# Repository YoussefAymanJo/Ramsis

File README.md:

# Ramsis
## Description
Desk Robot, your daily companion, can answer any question you ask about weather, news, or even songs. it powered by ESP32 S3. and has lovely face interact with you
## Why it was built
Actually,i feel boring and uncomfortable on my studying and working hours on my study or on pc.so,i made this robot to be ai companion for me. Interact with my emotiions and answer my questions.this robot mainly for entertainment and rapid helper companion in any quetion look like Jarvis.
## How to use it / Build it
first, fabricate and print pcb,then print 3d models,and wire circuit and test it.then assemlbe all together and test again.
## Schematic
I made a schematic for my keyboard, and sketch simpled diagram for schematic.

## PCB
I outlined shape first,the routed the pcb and added 3d models

Wiring Diagram :

## CAD
I started  sketching the enclosure based on the PCB, then made the top cover, added openings, and assembled.

## Firmware
i will us this for firmware https://github.com/78/xiaozhi-esp32 and https://github.com/EDISON-SCIENCE-CORNER/AI-CHAT-BOT/tree/main/3D%20FILES  while editing the code while building.
## BOM 
I made the BOM  and needed materials ,in egypt then convert its price to USD dollar.

## Zine

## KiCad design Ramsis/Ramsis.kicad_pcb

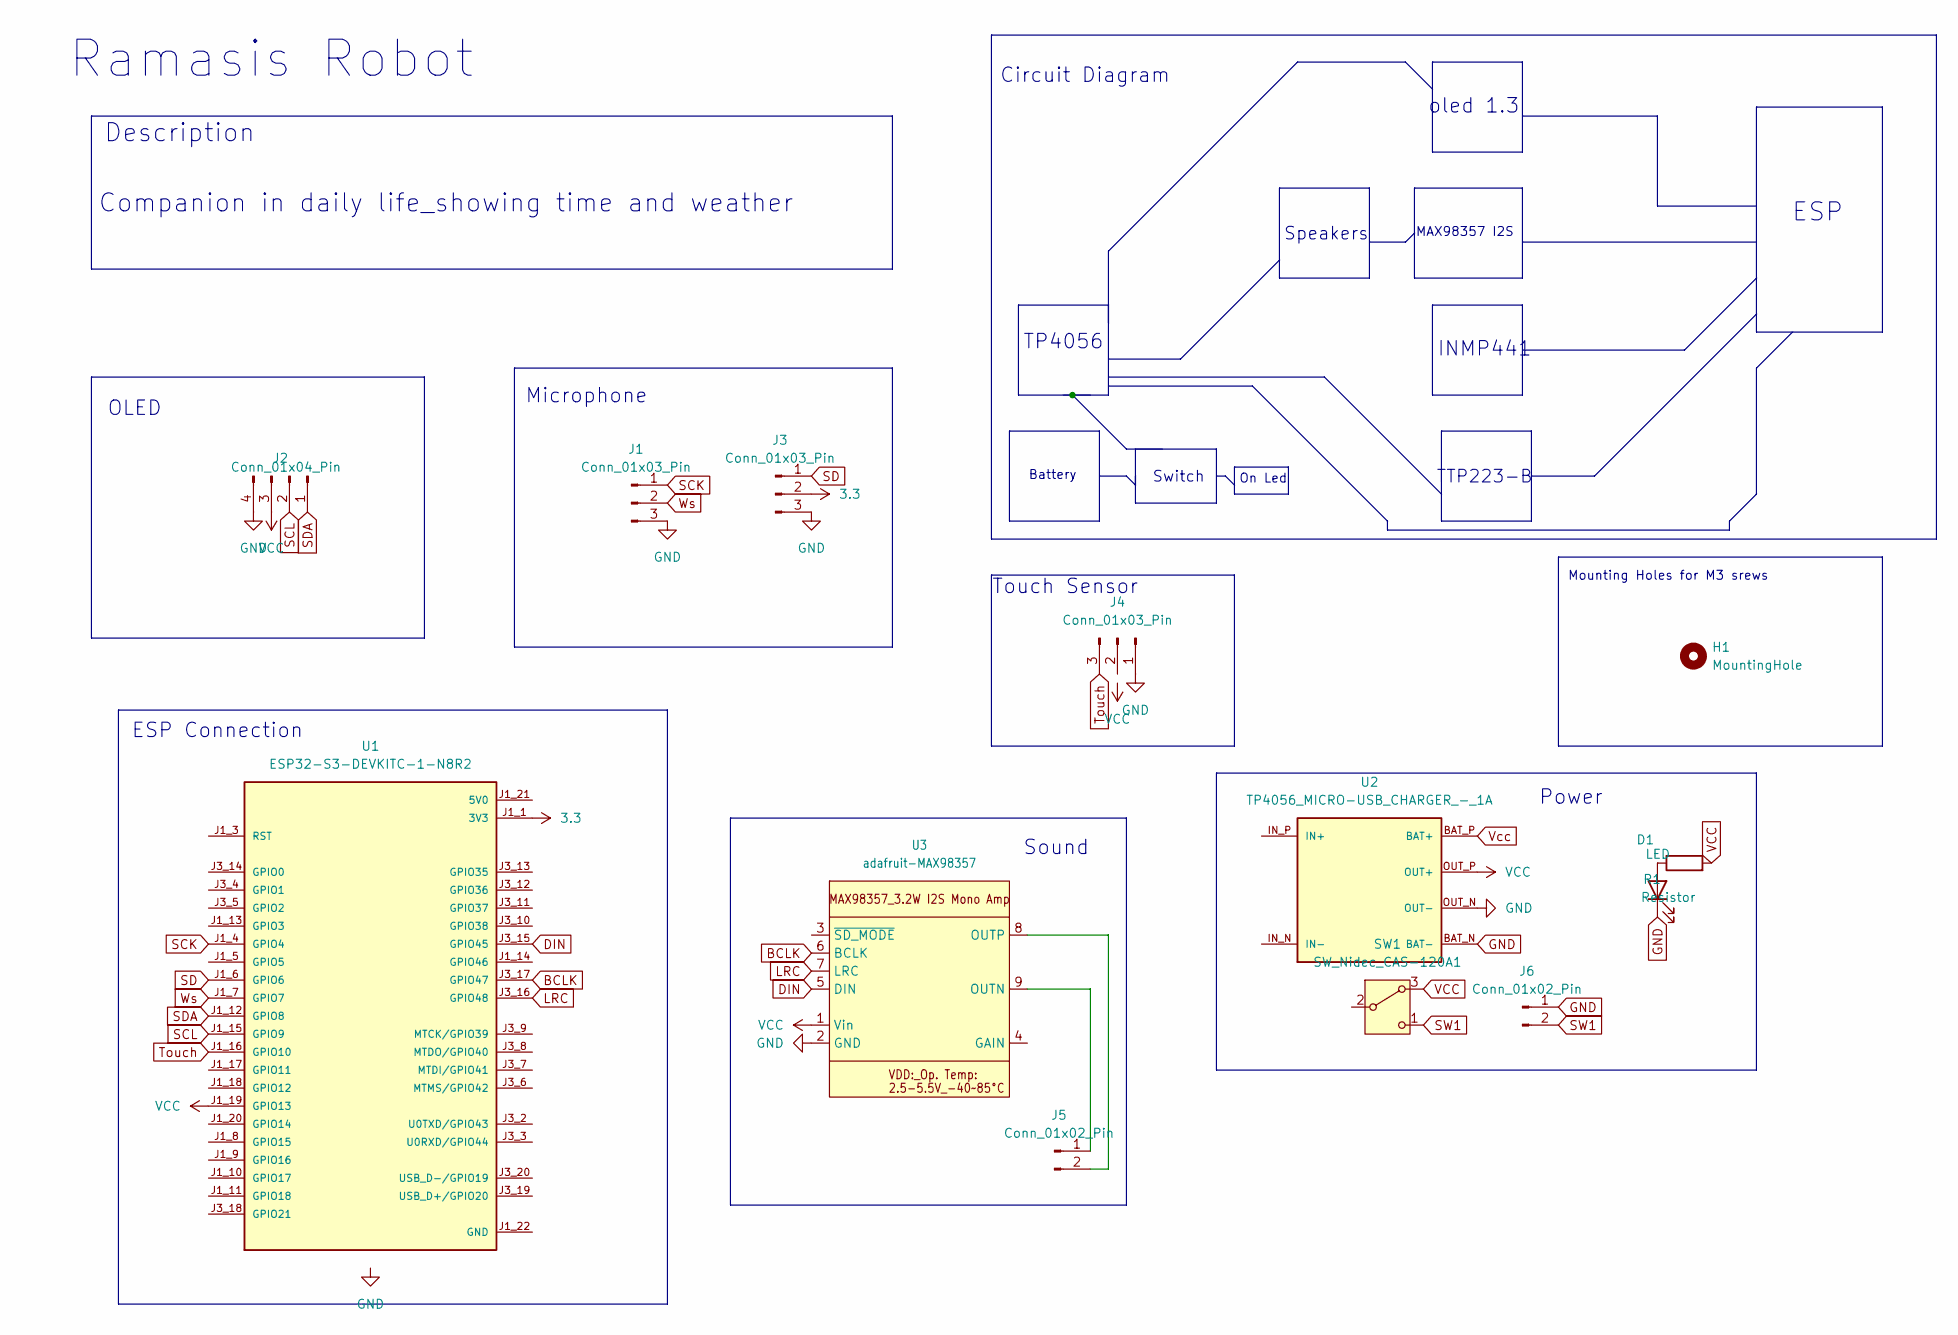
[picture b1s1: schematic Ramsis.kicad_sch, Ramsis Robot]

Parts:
D1: LED; LED_D3.0mm
H1: MountingHole; MountingHole_3.2mm_M3
J1, J3, J4: Conn_01x03_Pin; PinHeader_1x03_P2.00mm_Vertical
J2: Conn_01x04_Pin; PinHeader_1x04_P2.00mm_Vertical
J5, J6: Conn_01x02_Pin; JST_PH_S2B-PH-K_1x02_P2.00mm_Horizontal
R1: Resistor; R_Axial_DIN0204_L3.6mm_D1.6mm_P5.08mm_Horizontal
SW1: SW_Nidec_CAS-120A1; SW_Slide_SPDT_Angled_CK_OS102011MA1Q
U1: ESP32-S3-DEVKITC-1-N8R2; esp32 s55; PARTREV V1
U2: TP4056_MICRO-USB_CHARGER_-_1A; MODULE_TP4056_MICRO-USB_CHARGER_-_1A
U3: adafruit-MAX98357

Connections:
3.3: J3.2, U1.J1_1 (3V3), U1.J1_2 (3V3)
BCLK: U1.J3_17 (GPIO47), U3.6 (BCLK)
DIN: U1.J3_15 (GPIO45), U3.5 (DIN)
LRC: U1.J3_16 (GPIO48), U3.7 (LRC)
unnamed: D1.2 (A), R1.1
unnamed: J5.1, U3.9 (OUTN)
unnamed: J5.2, U3.8 (OUTP)
SCK: J1.1, U1.J1_4 (GPIO4)
SCL: J2.2, U1.J1_15 (GPIO9)
SD: J3.1, U1.J1_6 (GPIO6)
SDA: J2.1, U1.J1_12 (GPIO8)
SW1: J6.2, SW1.1 (C)
Touch: J4.3, U1.J1_16 (GPIO10)
VCC: J2.3, R1.2, SW1.3 (A), U1.J1_19 (GPIO13), U2.OUT_P (OUT+), U3.1 (Vin)
Vcc: U2.BAT_P (BAT+)
Ws: J1.2, U1.J1_7 (GPIO7)

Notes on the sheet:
INMP441
On Led
Microphone
oled 1.3
Ramasis Robot
Mounting Holes for M3 srews
Power
TTP223-B
Switch
Touch Sensor
Companion in daily life_showing time and weather
MAX98357 I2S
Circuit Diagram
ESP Connection
Description
Speakers
ESP
Battery
OLED
Sound
TP4056

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
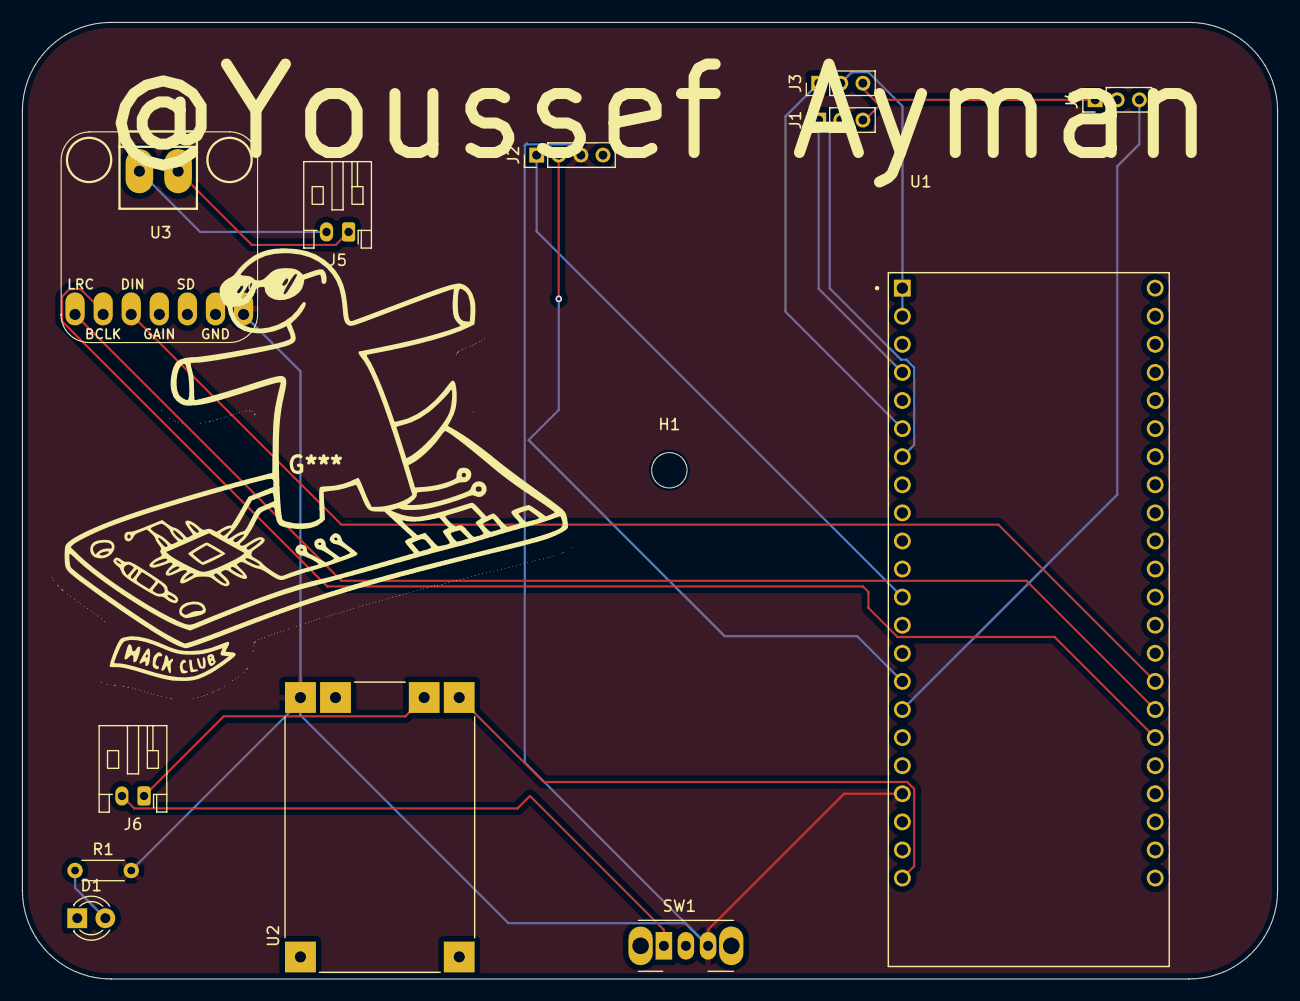
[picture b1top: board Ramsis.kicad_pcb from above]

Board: 2 copper layers, 113.5 x 86.5 mm, 13 parts (0 on the bottom side), 16 nets.

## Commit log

2026-06-21 udpate
2026-06-25 Update Zine image in README.md.
2026-06-25 Add new Zine image to README
2026-06-27 [ImgBot] Optimize images
    *Total -- 8,327.87kb -> 6,917.96kb (16.93%)
    /Images/Screenshot 2026-06-21 044231.png -- 38.10kb -> 16.15kb (57.61%)
    /qr-code.png -- 7.46kb -> 3.68kb (50.62%)
    /Footprints_libraries/voice/kicad-adafruit-MAX98357-main/screenshot.png -- 87.97kb -> 48.96kb (44.34%)
    /Footprints_libraries/max/kicad-adafruit-MAX98357-main/screenshot.png -- 87.97kb -> 48.96kb (44.34%)
    /Images/Screenshot 2026-06-21 050834.png -- 47.41kb -> 29.00kb (38.83%)
2026-06-27 Update README with wiring diagram
    Added wiring diagram image to the PCB section.
2026-06-27 ;feqf
